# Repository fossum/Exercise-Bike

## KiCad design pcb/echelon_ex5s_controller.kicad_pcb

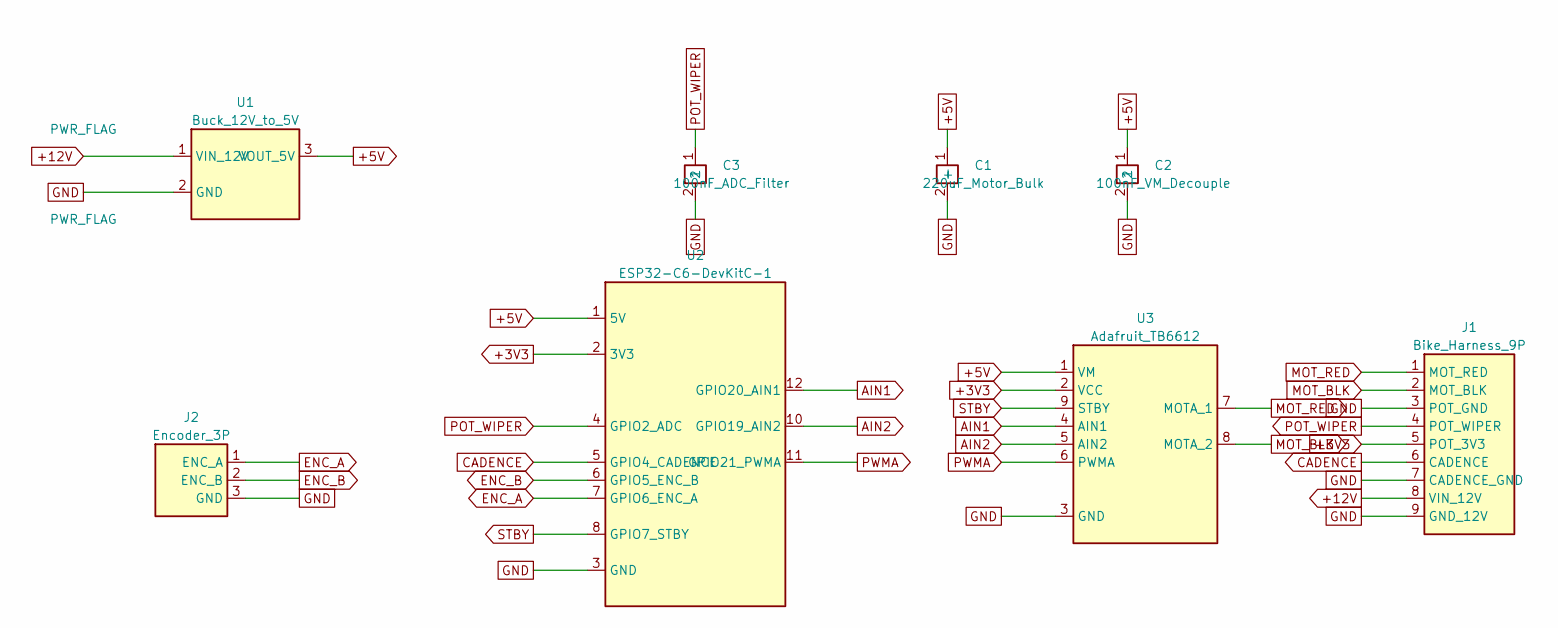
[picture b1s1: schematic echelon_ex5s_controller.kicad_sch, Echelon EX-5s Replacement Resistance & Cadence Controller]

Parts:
C1: 220uF_Motor_Bulk; CP_Radial_D8.0mm_P3.50mm
C2: 100nF_VM_Decouple; C_Disc_D5.0mm_W2.5mm_P5.00mm
C3: 100nF_ADC_Filter; C_Disc_D5.0mm_W2.5mm_P5.00mm
J1: Bike_Harness_9P; PinHeader_1x09_P2.54mm_Vertical
J2: Encoder_3P; PinHeader_1x03_P2.54mm_Vertical
U1: Buck_12V_to_5V
U2: ESP32-C6-DevKitC-1
U3: Adafruit_TB6612

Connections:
+3V3: J1.5 (POT_3V3), U2.2 (3V3), U3.2 (VCC)
+5V: C1.1 (+), C2.1, U1.3 (VOUT_5V), U2.1 (5V), U3.1 (VM)
+12V: J1.8 (VIN_12V), U1.1 (VIN_12V)
AIN1: U2.12 (GPIO20_AIN1), U3.4 (AIN1)
AIN2: U2.10 (GPIO19_AIN2), U3.5 (AIN2)
CADENCE: J1.6 (CADENCE), U2.5 (GPIO4_CADENCE)
ENC_A: J2.1 (ENC_A), U2.7 (GPIO6_ENC_A)
ENC_B: J2.2 (ENC_B), U2.6 (GPIO5_ENC_B)
GND: C1.2 (-), C2.2, C3.2, J1.3 (POT_GND), J1.7 (CADENCE_GND), J1.9 (GND_12V), J2.3 (GND), U1.2 (GND), U2.3 (GND), U3.3 (GND)
MOT_BLK: J1.2 (MOT_BLK), U3.8 (MOTA_2)
MOT_RED: J1.1 (MOT_RED), U3.7 (MOTA_1)
POT_WIPER: C3.1, J1.4 (POT_WIPER), U2.4 (GPIO2_ADC)
PWMA: U2.11 (GPIO21_PWMA), U3.6 (PWMA)
STBY: U2.8 (GPIO7_STBY), U3.9 (STBY)

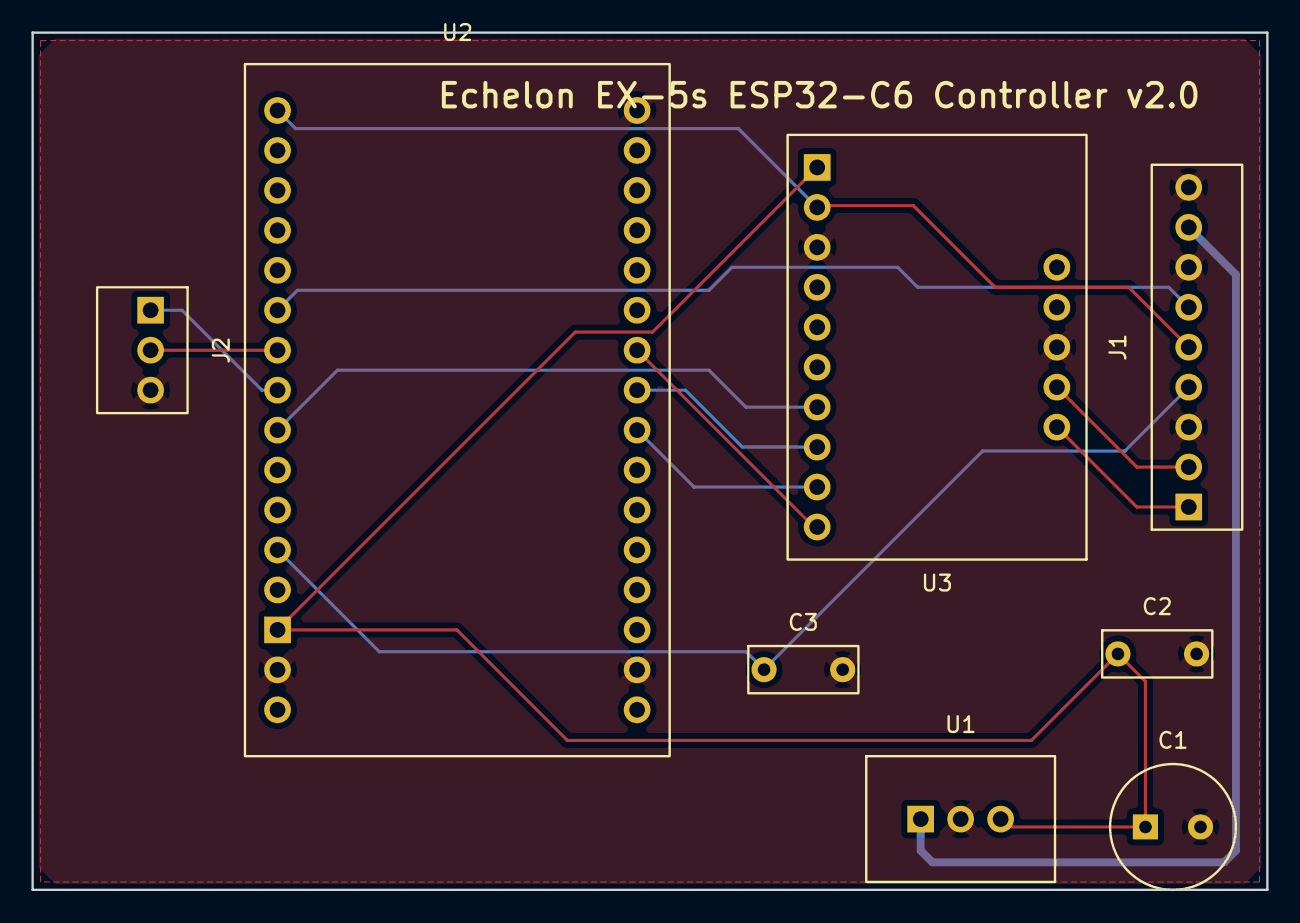
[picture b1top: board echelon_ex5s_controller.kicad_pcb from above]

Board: 2 copper layers, 78.5 x 54.5 mm, 8 parts (0 on the bottom side), 14 nets.

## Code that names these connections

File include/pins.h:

#ifndef PINS_H
#define PINS_H

#include <stdint.h>

// Target Board: ESP32-C6-DevKitC-1 (esp32-c6-devkitc-1)
// Note: Avoid GPIO 8 (onboard RGB LED) and GPIO 12/13 (native USB Serial/JTAG).

// 1. Resistance Potentiometer
constexpr uint8_t POT_PIN = 2; // Working potentiometer ADC1 wiper pin

// 2. Resistance Motor Driver (H-bridge)
constexpr uint8_t PIN_AIN1 = 20; // Forward ('f') increases Pot ADC
constexpr uint8_t PIN_AIN2 = 19; // Reverse ('r') decreases Pot ADC
constexpr uint8_t PIN_PWM  = 21; // H-bridge PWM speed control pin
constexpr uint8_t PIN_STBY = 7;  // H-bridge standby pin (HIGH = enabled, LOW = standby)

// 3. Rotary Encoder
constexpr uint8_t ENC_PIN_A = 6; // Phase A (CLK)
constexpr uint8_t ENC_PIN_B = 5; // Phase B (DT)
constexpr int ENC_PIN_SW = -1;   // Push button (SW), -1 when not wired

// 4. Cadence Sensor
constexpr uint8_t CADENCE_PIN = 4; // Reed switch pulse input (active-low with pullup)

#endif // PINS_H
